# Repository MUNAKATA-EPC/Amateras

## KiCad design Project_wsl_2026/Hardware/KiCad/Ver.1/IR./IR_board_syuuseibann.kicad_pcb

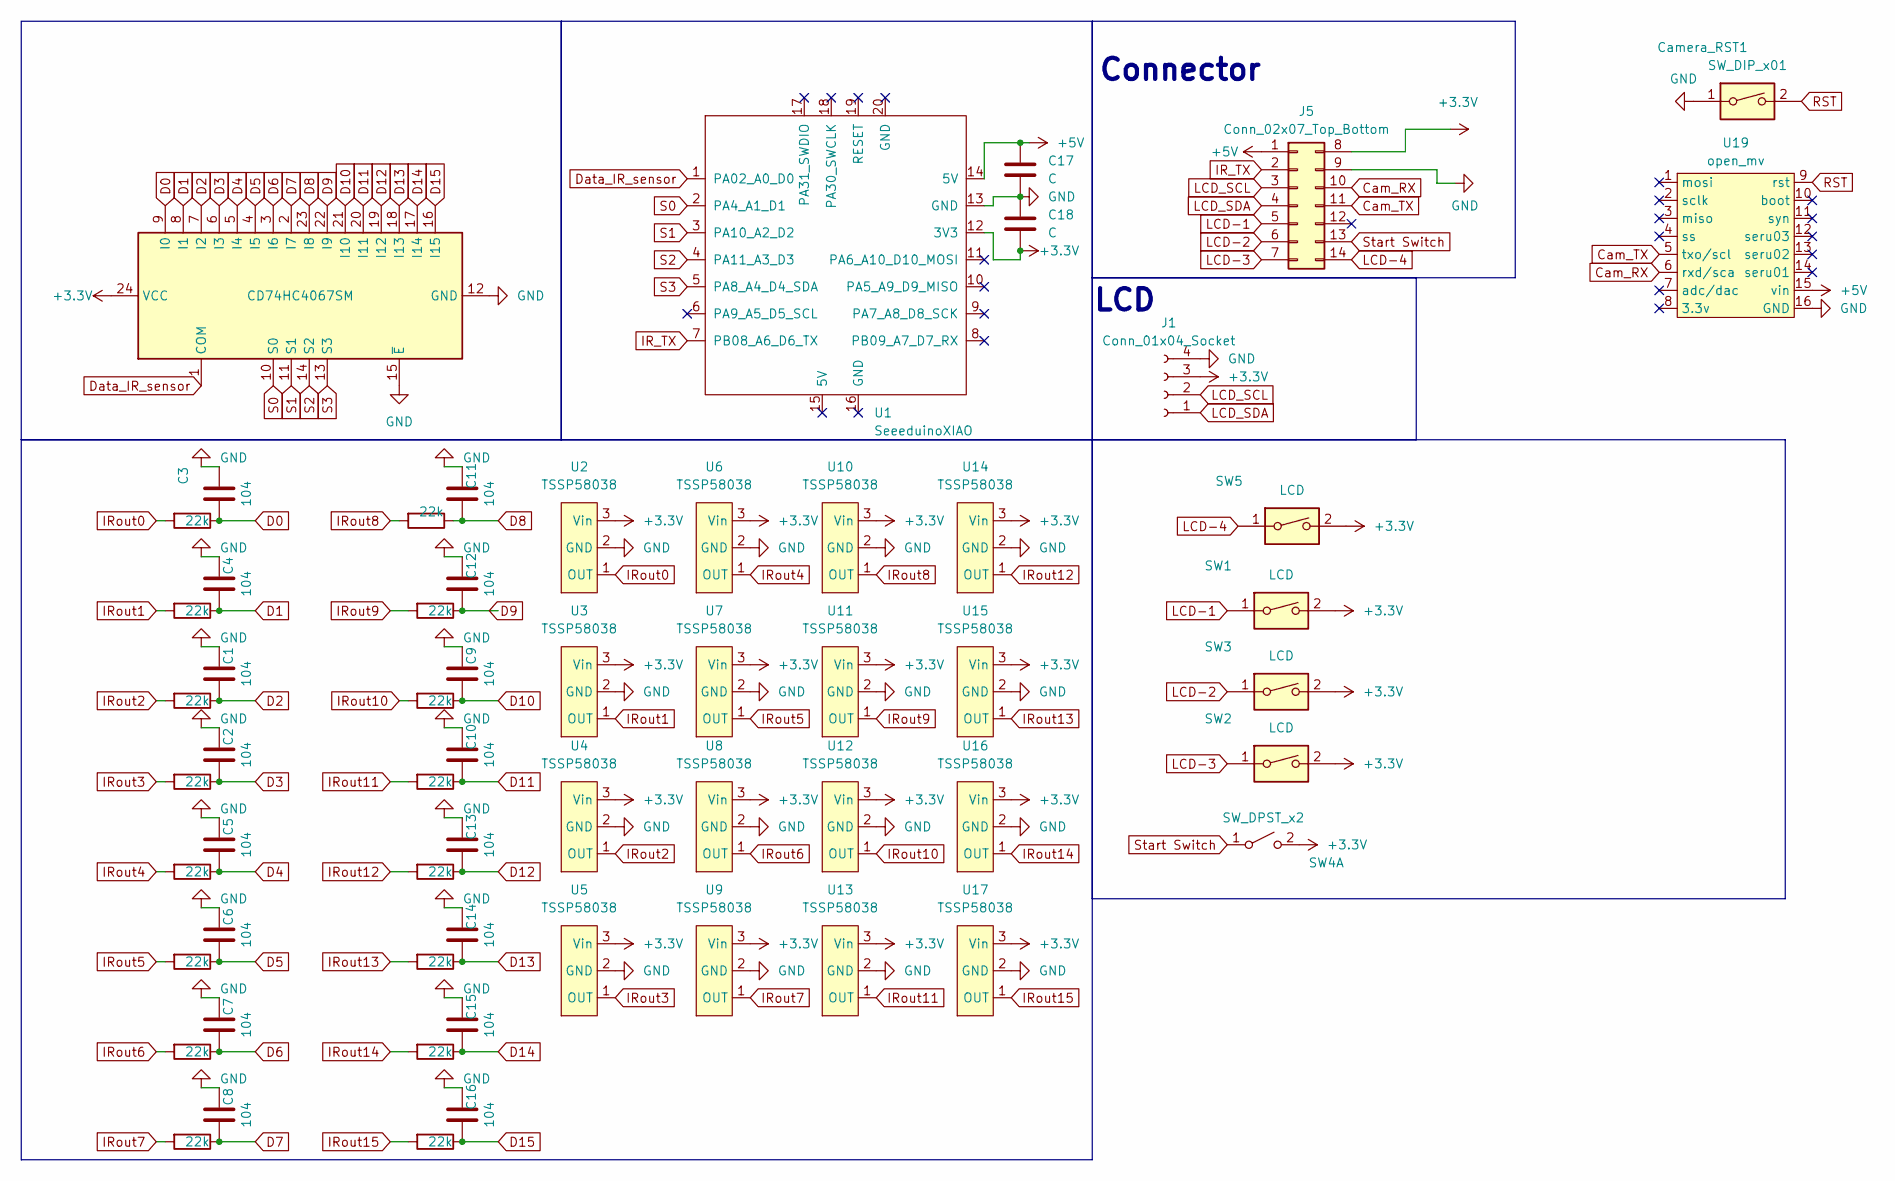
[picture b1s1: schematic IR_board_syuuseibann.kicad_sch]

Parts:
C1, C2, C3, C4, C5, C6, C7, C8, C9, C10, C11, C12, C13, C14, C15, C16: 104; C_0402_1005Metric; LCSC C1525
C17, C18: C; C_Disc_D5.0mm_W2.5mm_P2.50mm
Camera_RST1: SW_DIP_x01; SW_PUSH_6mm_H5mm
J1: Conn_01x04_Socket; PinHeader_1x04_P2.54mm_Vertical
J5: Conn_02x07_Top_Bottom; IDC-Header_2x07_P2.54mm_Vertical
R1, R2, R3, R4, R5, R6, R7, R8, R9, R10, R11, R12, R13, R14, R15, R16: 22k; R_0805_2012Metric; LCSC C25611
SW1, SW2, SW3, SW5: LCD; SW_PUSH_6mm_H5mm
SW4: SW_DPST_x2; PinSocket_1x03_P2.54mm_Vertical
U1: SeeeduinoXIAO; Seeeduino Xiao
U2, U3, U4, U5, U6, U7, U8, U9, U10, U11, U12, U13, U14, U15, U16, U17: TSSP58038; PinHeader_1x03_P2.54mm_Vertical
U18: CD74HC4067SM; SSOP-24_5.3x8.2mm_P0.65mm
U19: open_mv; Open MV

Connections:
+3.3V: C18.2, J1.3, J5.8, SW1.2, SW2.2, SW3.2, SW4.2 (B), SW5.2, U1.12 (3V3), U2.3 (Vin), U3.3 (Vin), U4.3 (Vin), U5.3 (Vin), U6.3 (Vin), U7.3 (Vin), U8.3 (Vin), U9.3 (Vin), U10.3 (Vin), U11.3 (Vin), U12.3 (Vin), U13.3 (Vin), U14.3 (Vin), U15.3 (Vin), U16.3 (Vin), U17.3 (Vin), U18.24 (VCC)
+5V: C17.1, J5.1, U1.14 (5V), U19.15 (vin)
Cam_RX: J5.10, U19.6 (rxd/sca)
Cam_TX: J5.11, U19.5 (txo/scl)
D0: C3.1, R3.1, U18.9 (I0)
D1: C4.1, R4.1, U18.8 (I1)
D2: C1.1, R1.1, U18.7 (I2)
D3: C2.1, R2.1, U18.6 (I3)
D4: C5.1, R5.1, U18.5 (I4)
D5: C6.1, R6.1, U18.4 (I5)
D6: C7.1, R7.1, U18.3 (I6)
D7: C8.1, R8.1, U18.2 (I7)
D8: C11.1, R11.1, U18.23 (I8)
D9: C12.1, R12.1, U18.22 (I9)
D10: C9.1, R9.1, U18.21 (I10)
D11: C10.1, R10.1, U18.20 (I11)
D12: C13.1, R13.1, U18.19 (I12)
D13: C14.1, R14.1, U18.18 (I13)
D14: C15.1, R15.1, U18.17 (I14)
D15: C16.1, R16.1, U18.16 (I15)
Data_IR_sensor: U1.1 (PA02_A0_D0), U18.1 (COM)
GND: C1.2, C2.2, C3.2, C4.2, C5.2, C6.2, C7.2, C8.2, C9.2, C10.2, C11.2, C12.2, C13.2, C14.2, C15.2, C16.2, C17.2, C18.1, Camera_RST1.1, J1.4, J5.9, U1.13 (GND), U2.2 (GND), U3.2 (GND), U4.2 (GND), U5.2 (GND), U6.2 (GND), U7.2 (GND), U8.2 (GND), U9.2 (GND), U10.2 (GND), U11.2 (GND), U12.2 (GND), U13.2 (GND), U14.2 (GND), U15.2 (GND), U16.2 (GND), U17.2 (GND), U18.12 (GND), U18.15 (~E), U19.16 (GND); also elsewhere on the board
IR_TX: J5.2, U1.7 (PB08_A6_D6_TX)
IRout0: R3.2, U2.1 (OUT)
IRout1: R4.2, U3.1 (OUT)
IRout2: R1.2, U4.1 (OUT)
IRout3: R2.2, U5.1 (OUT)
IRout4: R5.2, U6.1 (OUT)
IRout5: R6.2, U7.1 (OUT)
IRout6: R7.2, U8.1 (OUT)
IRout7: R8.2, U9.1 (OUT)
IRout8: R11.2, U10.1 (OUT)
IRout9: R12.2, U11.1 (OUT)
IRout10: R9.2, U12.1 (OUT)
IRout11: R10.2, U13.1 (OUT)
IRout12: R13.2, U14.1 (OUT)
IRout13: R14.2, U15.1 (OUT)
IRout14: R15.2, U16.1 (OUT)
IRout15: R16.2, U17.1 (OUT)
LCD-1: J5.5, SW1.1
LCD-2: J5.6, SW3.1
LCD-3: J5.7, SW2.1
LCD-4: J5.14, SW5.1
LCD_SCL: J1.2, J5.3
LCD_SDA: J1.1, J5.4
RST: Camera_RST1.2, U19.9 (rst); also elsewhere on the board
S0: U1.2 (PA4_A1_D1), U18.10 (S0)
S1: U1.3 (PA10_A2_D2), U18.11 (S1)
S2: U1.4 (PA11_A3_D3), U18.14 (S2)
S3: U1.5 (PA8_A4_D4_SDA), U18.13 (S3)
Start Switch: J5.13, SW4.1 (A)

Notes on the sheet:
LCD
Connector

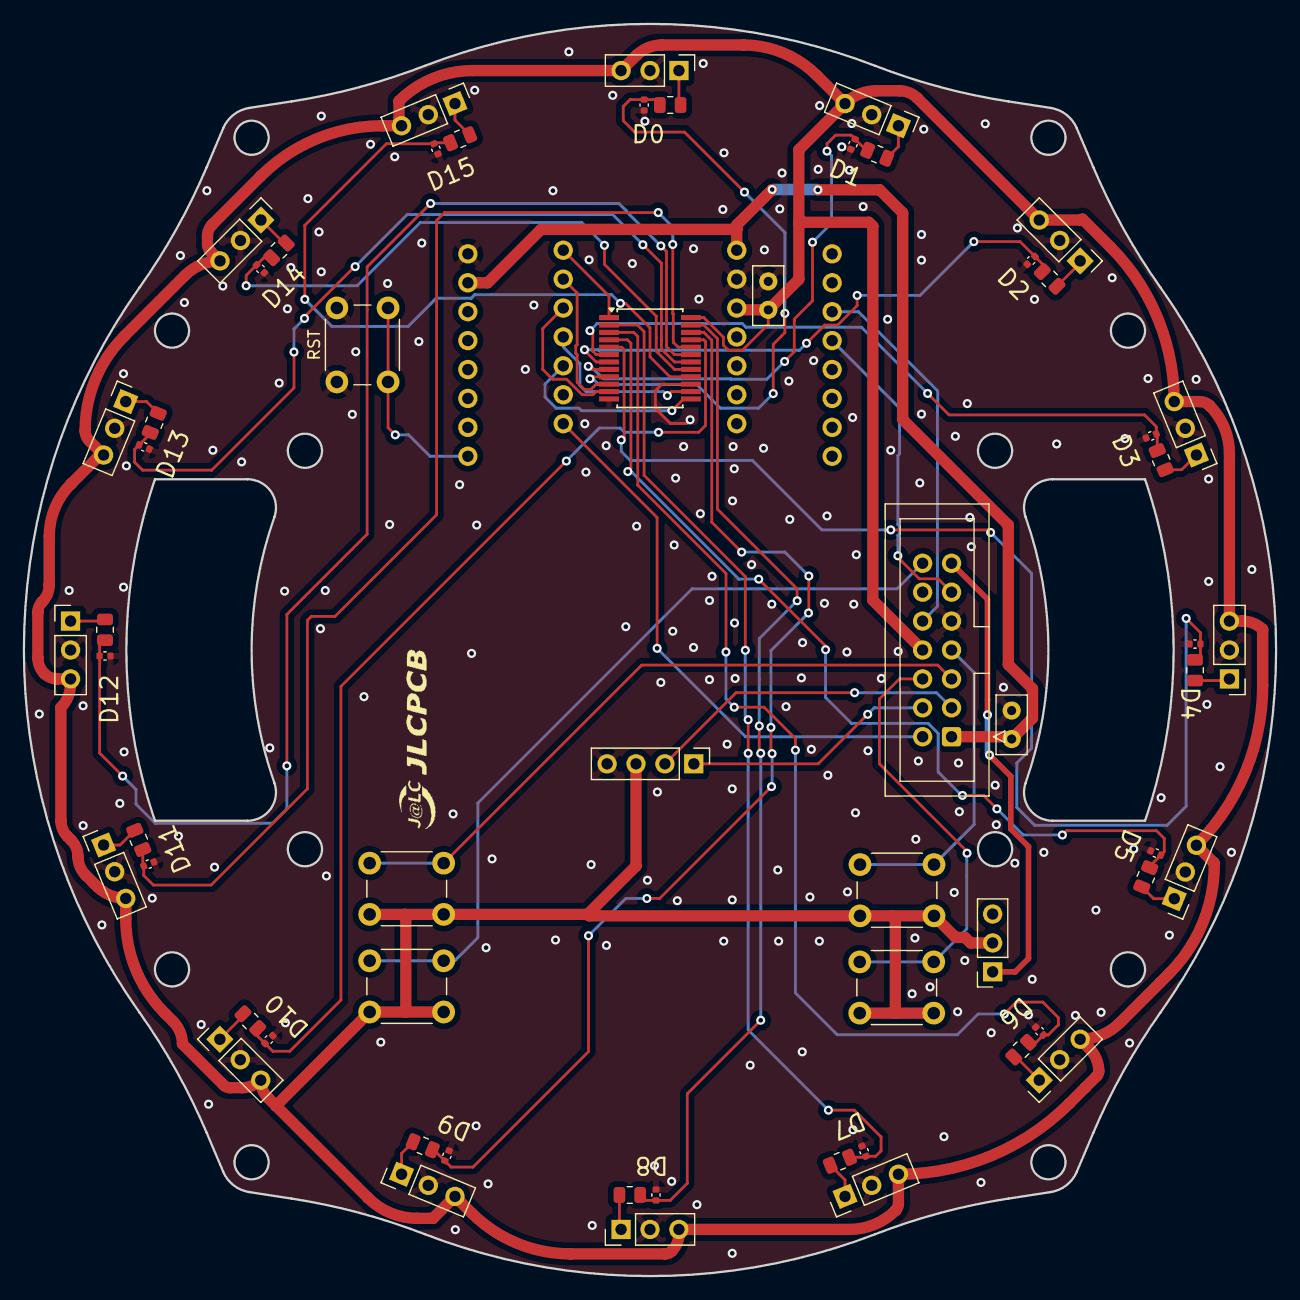
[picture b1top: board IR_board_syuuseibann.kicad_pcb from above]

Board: 2 copper layers, 110.0 x 110.0 mm, 61 parts (1 on the bottom side), 51 nets.

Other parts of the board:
RST: SW_DIP_x01; SW_PUSH_6mm_H5mm

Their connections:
GND: RST.1; also elsewhere on the board
RST: RST.2; also elsewhere on the board

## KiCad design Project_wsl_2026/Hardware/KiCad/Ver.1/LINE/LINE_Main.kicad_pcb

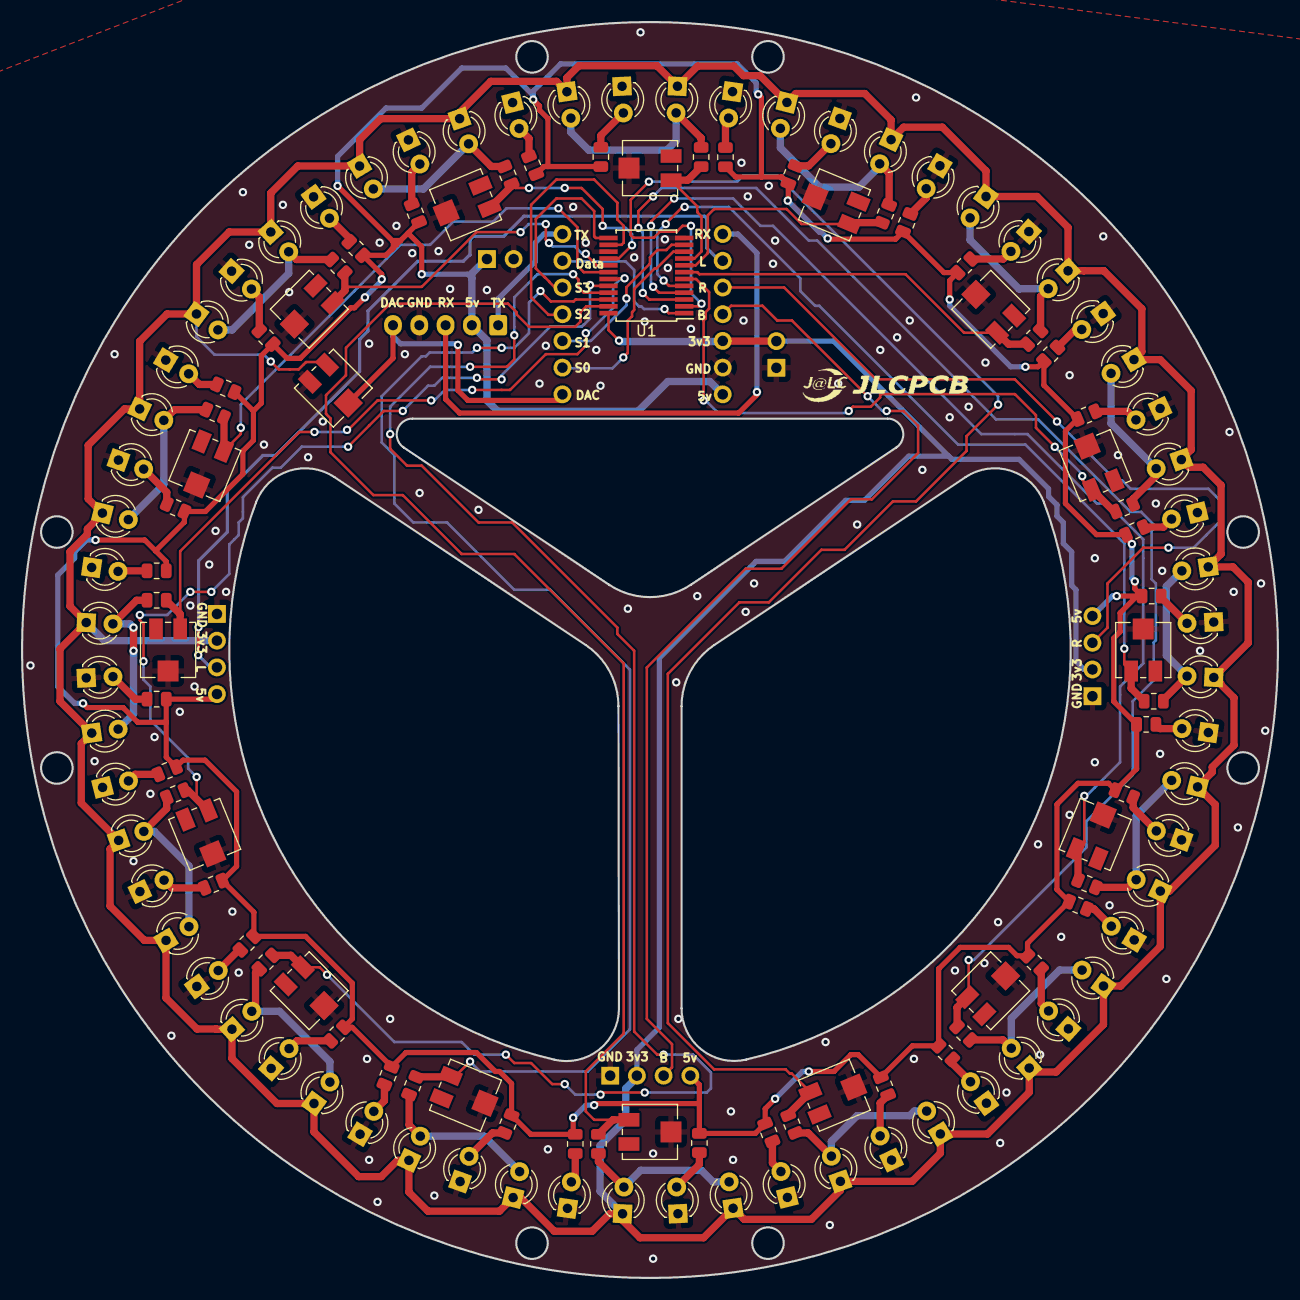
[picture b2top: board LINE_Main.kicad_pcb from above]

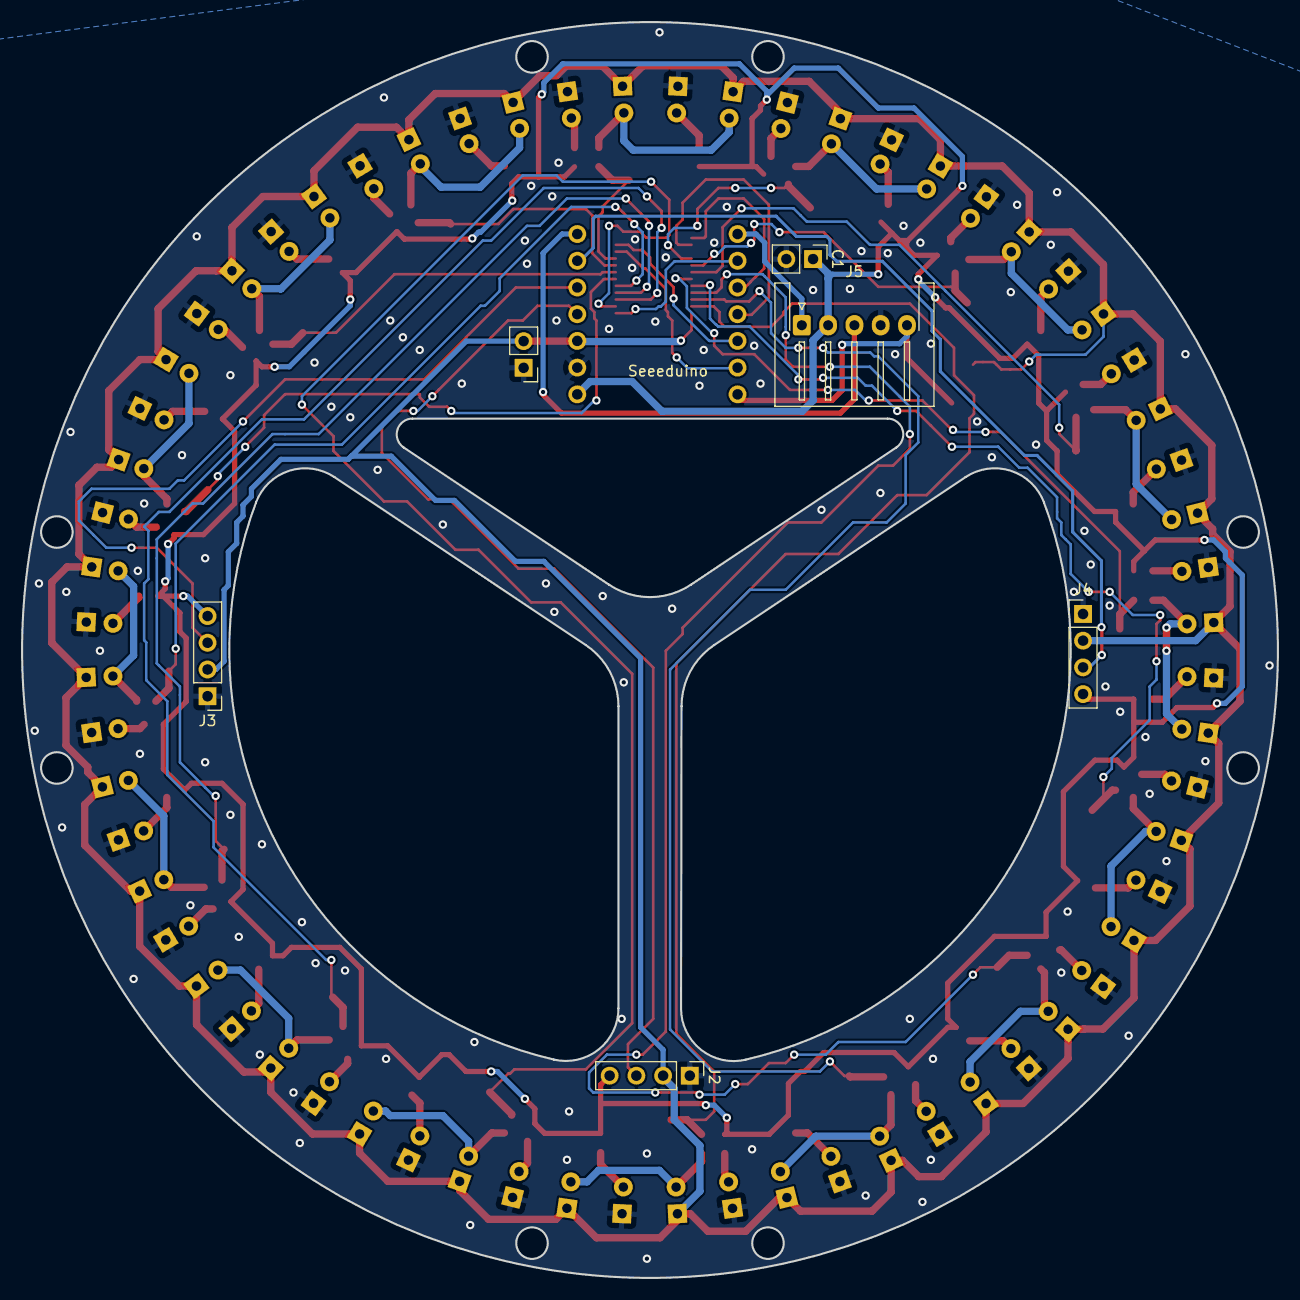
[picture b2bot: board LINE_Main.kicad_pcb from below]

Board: 2 copper layers, 119.4 x 119.4 mm, 137 parts (6 on the bottom side), 78 nets.

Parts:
C1, C2: C; PinHeader_1x02_P2.54mm_Vertical
D1, D2, D3, D4, D5, D6, D7, D8, D9, D10, D11, D12, D13, D14, D15, D16, D17, D18, D19, D20, D21, D22, D23, D24, D25, D26, D27, D28, D29, D30, D31, D32: LED; LED_D3.0mm_Clear
J2, J3, J4: Conn_01x04_Socket; PinHeader_1x04_P2.54mm_Vertical
J5: Conn_01x05_Socket; JST_XH_S5B-XH-A-1_1x05_P2.50mm_Horizontal
Q1, Q2, Q3, Q4, Q5, Q6, Q7, Q8, Q9, Q10, Q11, Q12, Q13, Q14, Q15, Q16, Q17, Q18, Q19, Q20, Q21, Q22, Q23, Q24, Q25, Q26, Q27, Q28, Q29, Q30, Q31, Q32: Q_Photo_NPN; LED_D3.0mm_Clear
R1, R2, R3, R4, R5, R6, R7, R8, R9, R10, R11, R12, R13, R14, R15, R16, R17, R18, R19, R20, R21, R22, R23, R24, R25, R26, R27, R28, R29, R30, R31, R32, R33, R34, R35, R36, R37, R38, R39, R40, R41, R42, R43, R44, R45, R46, R47, R48: R; R_0805_2012Metric
RV1, RV2, RV3, RV4, RV5, RV6, RV7, RV8, RV9, RV10, RV11, RV12, RV13, RV14, RV15, RV16, RV17: R_Potentiometer_Trim_US; Potentiometer_Vishay_TS53YJ_Vertical
U1: CD74HC4067SM; SSOP-24_5.3x8.2mm_P0.65mm
U2: Seeeduino_Xiao; Seeeduino Xiao v2

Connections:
1: R1.2, RV1.3, U1.9 (I0)
2: R2.2, RV2.3, U1.8 (I1)
3: R3.2, RV3.3, U1.7 (I2)
4: R4.2, RV4.3, U1.6 (I3)
5: R5.2, RV5.3, U1.5 (I4)
6: R6.2, RV6.3, U1.4 (I5)
7: R7.2, RV7.3, U1.3 (I6)
8: R8.2, RV8.3, U1.2 (I7)
9: R9.2, RV9.3, U1.23 (I8)
10: R10.2, RV10.3, U1.22 (I9)
11: R11.2, RV11.3, U1.21 (I10)
12: R12.2, RV12.3, U1.20 (I11)
13: R13.2, RV13.3, U1.19 (I12)
14: R14.2, RV14.3, U1.18 (I13)
15: R15.2, RV15.3, U1.17 (I14)
16: R16.2, RV16.3, U1.16 (I15)
+3.3V: C2.2, J2.2, J3.2, J4.2, Q1.1 (C), Q2.1 (C), Q3.1 (C), Q4.1 (C), Q5.1 (C), Q6.1 (C), Q7.1 (C), Q8.1 (C), Q9.1 (C), Q10.1 (C), Q11.1 (C), Q12.1 (C), Q13.1 (C), Q14.1 (C), Q15.1 (C), Q16.1 (C), Q17.1 (C), Q18.1 (C), Q19.1 (C), Q20.1 (C), Q21.1 (C), Q22.1 (C), Q23.1 (C), Q24.1 (C), Q25.1 (C), Q26.1 (C), Q27.1 (C), Q28.1 (C), Q29.1 (C), Q30.1 (C), Q31.1 (C), Q32.1 (C), RV17.3, U1.24 (VCC), U2.12 (3V3)
+5V: C1.1, J2.4, J3.4, J4.4, J5.2, R17.1, R18.1, R19.1, R20.1, R21.1, R22.1, R23.1, R24.1, R25.1, R26.1, R27.1, R28.1, R29.1, R30.1, R31.1, R32.1, R33.1, R34.1, R35.1, R36.1, R37.1, R38.1, R39.1, R40.1, R41.1, R42.1, R43.1, R44.1, R45.1, R46.1, R47.1, R48.1, U2.14 (5V)
DAC: J5.5, RV17.2, U2.1 (DAC)
Data_Line_sensor: U1.1 (COM), U2.6 (SCL)
GND: C1.2, C2.1, D1.1 (K), D2.1 (K), D3.1 (K), D4.1 (K), D5.1 (K), D6.1 (K), D7.1 (K), D8.1 (K), D9.1 (K), D10.1 (K), D11.1 (K), D12.1 (K), D13.1 (K), D14.1 (K), D15.1 (K), D16.1 (K), D17.1 (K), D18.1 (K), D19.1 (K), D20.1 (K), D21.1 (K), D22.1 (K), D23.1 (K), D24.1 (K), D25.1 (K), D26.1 (K), D27.1 (K), D28.1 (K), D29.1 (K), D30.1 (K), D31.1 (K), D32.1 (K), J2.1, J3.1, J4.1, J5.4, RV1.2, RV2.2, RV3.2, RV4.2, RV5.2, RV6.2, RV7.2, RV8.2, RV9.2, RV10.2, RV11.2, RV12.2, RV13.2, RV14.2, RV15.2, RV16.2, RV17.1, U1.12 (GND), U1.15 (~E), U2.13 (GND)
Line_RX: J5.3, U2.8 (RX)
Line_TX: J5.1, U2.7 (TX)
unnamed: D1.2 (A), R17.2
unnamed: D2.2 (A), R18.2
unnamed: D3.2 (A), R19.2
unnamed: D4.2 (A), R20.2
unnamed: D5.2 (A), R21.2
unnamed: D6.2 (A), R22.2
unnamed: D7.2 (A), R23.2
unnamed: D8.2 (A), R24.2
unnamed: D9.2 (A), R25.2
unnamed: D10.2 (A), R26.2
unnamed: D11.2 (A), R27.2
unnamed: D12.2 (A), R28.2
unnamed: D13.2 (A), R29.2
unnamed: D14.2 (A), R30.2
unnamed: D15.2 (A), R31.2
unnamed: D16.2 (A), R32.2
unnamed: D17.2 (A), R33.2
unnamed: D18.2 (A), R34.2
unnamed: D19.2 (A), R35.2
unnamed: D20.2 (A), R36.2
unnamed: D21.2 (A), R37.2
unnamed: D22.2 (A), R38.2
unnamed: D23.2 (A), R39.2
unnamed: D24.2 (A), R40.2
unnamed: D25.2 (A), R41.2
unnamed: D26.2 (A), R42.2
unnamed: D27.2 (A), R43.2
unnamed: D28.2 (A), R44.2
unnamed: D29.2 (A), R45.2
unnamed: D30.2 (A), R46.2
unnamed: D31.2 (A), R47.2
unnamed: D32.2 (A), R48.2
unnamed: Q1.2 (E), Q2.2 (E), R1.1
unnamed: Q3.2 (E), Q4.2 (E), R2.1
unnamed: Q5.2 (E), Q6.2 (E), R3.1
unnamed: Q7.2 (E), Q8.2 (E), R4.1
unnamed: Q9.2 (E), Q10.2 (E), R5.1
unnamed: Q11.2 (E), Q12.2 (E), R6.1
unnamed: Q13.2 (E), Q14.2 (E), R7.1
unnamed: Q15.2 (E), Q16.2 (E), R8.1
unnamed: Q17.2 (E), Q18.2 (E), R9.1
unnamed: Q19.2 (E), Q20.2 (E), R10.1
unnamed: Q21.2 (E), Q22.2 (E), R11.1
unnamed: Q23.2 (E), Q24.2 (E), R12.1
unnamed: Q25.2 (E), Q26.2 (E), R13.1
unnamed: Q27.2 (E), Q28.2 (E), R14.1
unnamed: Q29.2 (E), Q30.2 (E), R15.1
unnamed: Q31.2 (E), Q32.2 (E), R16.1
S0: U1.10 (S0), U2.2
S1: U1.11 (S1), U2.3
S2: U1.14 (S2), U2.4
S3: U1.13 (S3), U2.5 (SDA)
Sensor_Back: J2.3, U2.11 (MOSI)
Sensor_Left: J4.3, U2.9 (SCK)
Sensor_Right: J3.3, U2.10 (MISO)

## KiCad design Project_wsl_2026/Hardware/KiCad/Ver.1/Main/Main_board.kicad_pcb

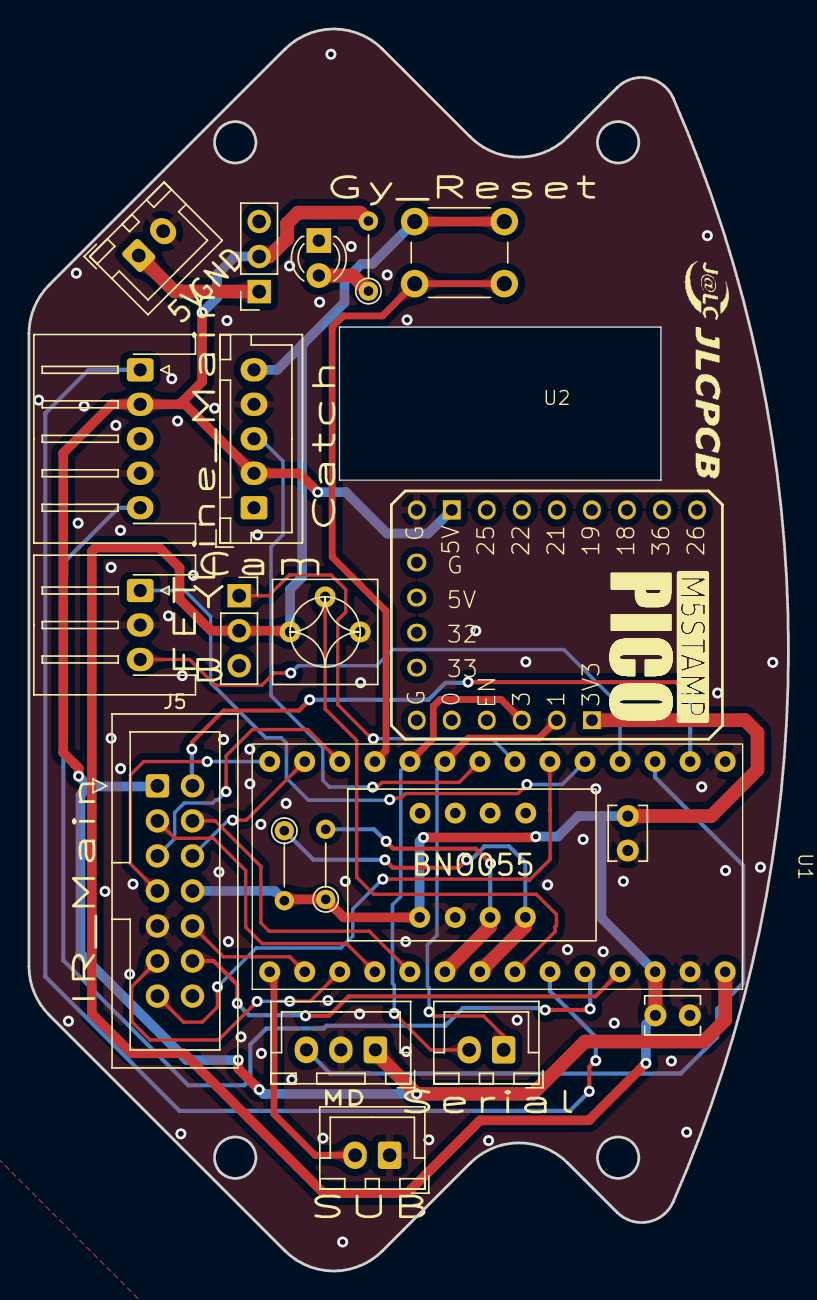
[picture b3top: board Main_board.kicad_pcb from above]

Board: 2 copper layers, 55.1 x 90.0 mm, 21 parts (0 on the bottom side), 29 nets.

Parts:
BNO1: BNO055
C1, C3: C; C_Disc_D3.8mm_W2.6mm_P2.50mm
D1: LED; LED_D3.0mm_Clear
J1: Conn_01x03_Socket; JST_XH_B3B-XH-A_1x03_P2.50mm_Vertical
J2, J6, J7: Conn_01x02_Socket; JST_XH_B2B-XH-A_1x02_P2.50mm_Vertical
J3: Conn_01x03_Socket; JST_XH_S3B-XH-A-1_1x03_P2.50mm_Horizontal
J4: Conn_01x05_Socket; JST_XH_S5B-XH-A-1_1x05_P2.50mm_Horizontal
J5: Conn_02x07_Top_Bottom; IDC-Header_2x07_P2.54mm_Vertical
J8: Conn_01x05_Socket; JST_XH_B5B-XH-A_1x05_P2.50mm_Vertical
R1, R2: 10K; R_Axial_DIN0204_L3.6mm_D1.6mm_P5.08mm_Vertical
R3: R; R_Axial_DIN0204_L3.6mm_D1.6mm_P5.08mm_Vertical
RV1: R_Potentiometer_Trim_US; RV
SW1: SW_Push; SW_PUSH_6mm_H5mm
SW2, SW4: SW_DPST_x2; PinSocket_1x03_P2.54mm_Vertical
U1: Teensy4.0
U2: Stamp_Pico; Stamp Pico

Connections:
5V_IN: J2.1, SW4.1 (A)
+3.3V: BNO1.1 (VIN), C1.1, C3.2, J5.8, J8.5, R1.1, R2.2, RV1.3, SW1.1, SW2.2 (B), U1.31 (3V3), U2.19 (3V3)
+5V: J1.1, J4.2, J5.1, J8.2, R3.2, SW4.2 (B), U1.33 (VIN), U2.8 (5V)
A6: RV1.2, U1.27 (20_A6_TX5_LRCLK1)
Cam Switch: SW2.1 (A), U1.7 (5_IN2)
Cam_RX: J5.10, U1.21 (14_A0_TX3_SPDIF_OUT)
Cam_TX: J5.11, U1.22 (15_A1_RX3_SPDIF_IN)
Catch: J8.3, U1.8 (6_OUT1D)
Catch_sub: J7.2, U1.20 (13_SCK_CRX1_LED)
FET_1: J3.3, U1.4 (2_OUT2)
FET_2: J3.1, U1.5 (3_LRCLK2)
GND: BNO1.2 (GND), C1.2, C3.1, D1.1 (K), J1.2, J2.2, J3.2, J4.4, J5.9, J7.1, J8.4, RV1.1, U1.1 (GND), U2.9 (GND)
Gyro_SCL: BNO1.4 (SCL), R2.1, U1.26 (19_A5_SCL0)
Gyro_SDA: BNO1.3 (SDA), R1.2, U1.25 (18_A4_SDA0)
Gyro_reset: SW1.2, U1.11 (9_OUT1C)
IR_DAC: J5.12, U1.30 (23_A9_CRX1_MCLK1)
IR_TX: J5.2, U1.2 (0_RX1_CRX2_CS1)
LCD-1: J5.5, U1.12 (10_CS_MQSR)
LCD-2: J5.6, U1.13 (11_MOSI_CTX1)
LCD-3: J5.7, U1.14 (12_MISO_MQSL)
LCD_SCL: J5.3, U1.23 (16_A2_RX4_SCL1)
LCD_SDA: J5.4, U1.24 (17_A3_TX4_SDA1)
Line_DAC: J4.5, U1.29 (22_A8_CTX1)
Line_TX: J4.1, U1.28 (21_A7_RX5_BCLK1)
unnamed: D1.2 (A), R3.1
RX2: J6.1, U1.9 (7_RX2_OUT1A), U2.18 (G1)
Start Switch: J5.13, U1.6 (4_BCLK2)
TX2: J6.2, U1.10 (8_TX2_IN1), U2.17 (G3)
TX_MD: J1.3, U1.3 (1_TX1_CTX2_MISO1)

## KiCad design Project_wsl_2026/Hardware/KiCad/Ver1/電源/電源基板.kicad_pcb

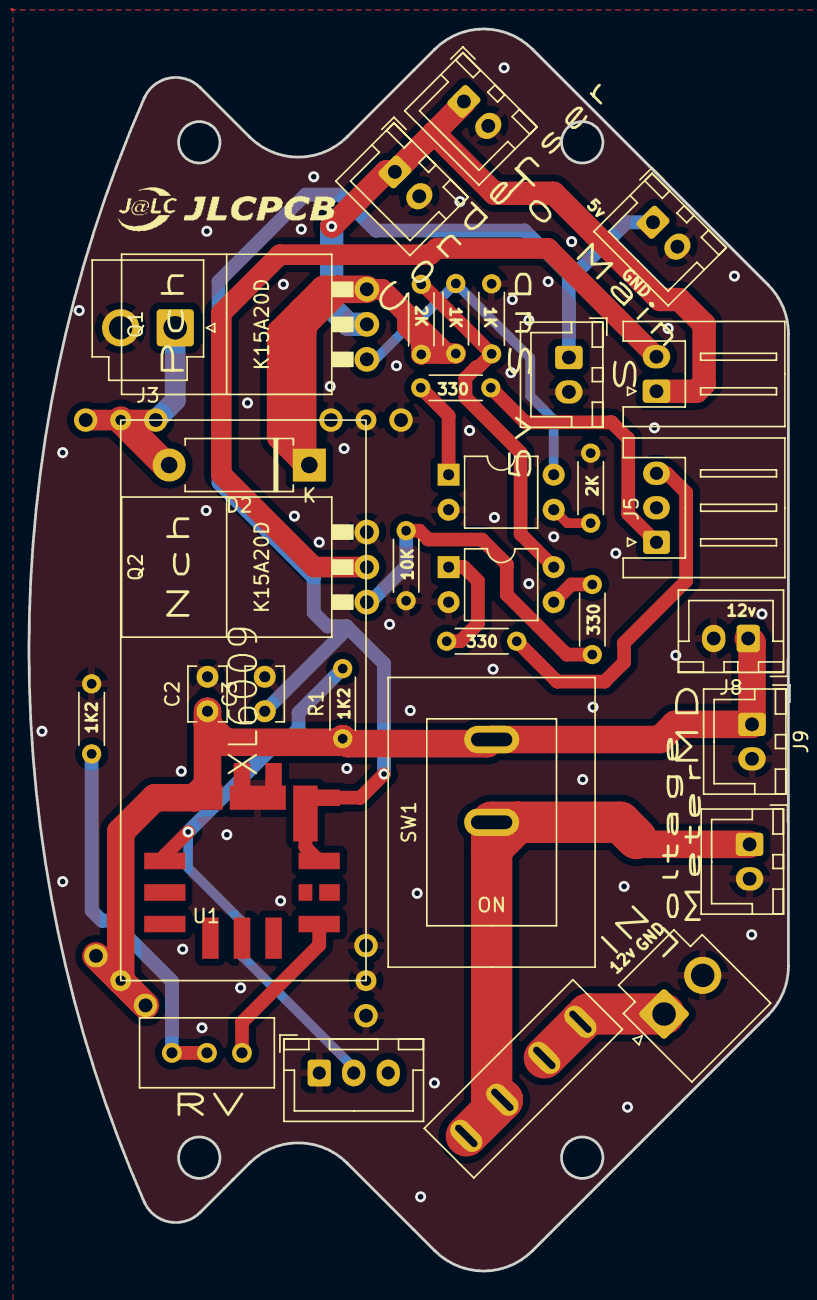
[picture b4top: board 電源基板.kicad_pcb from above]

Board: 2 copper layers, 55.1 x 90.0 mm, 34 parts (0 on the bottom side), 21 nets.

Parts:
BT1: Battery; JST_VH_B2P-VH_1x02_P3.96mm_Vertical
C1, C4: C; JST_XH_B2B-XH-A_1x02_P2.50mm_Vertical
C2, C3: C; C_Disc_D3.8mm_W2.6mm_P2.50mm
D2: D; D_DO-15_P10.16mm_Horizontal
F1: Fuse; fuse_socket
J1, J4, J8, J9: Conn_01x02_Socket; JST_XH_B2B-XH-A_1x02_P2.50mm_Vertical
J3: Conn_01x02_Socket; JST_VH_B2P-VH_1x02_P3.96mm_Vertical
J5: Conn_01x03_Socket; JST_XH_S3B-XH-A_1x03_P2.50mm_Horizontal
J6: 電圧計; JST_XH_B2B-XH-A_1x02_P2.50mm_Vertical
J7: Conn_01x02_Socket; JST_XH_S2B-XH-A_1x02_P2.50mm_Horizontal
Q1: PMOS; K15A20D
Q2: NMOS; K15A20D
R1, R2: R; R_Axial_DIN0204_L3.6mm_D1.6mm_P5.08mm_Horizontal
R3, R7: 2K; R_Axial_DIN0204_L3.6mm_D1.6mm_P5.08mm_Horizontal
R4, R8: 1K; R_Axial_DIN0204_L3.6mm_D1.6mm_P5.08mm_Horizontal
R5, R6, R9: 330; R_Axial_DIN0204_L3.6mm_D1.6mm_P5.08mm_Horizontal
R10: 10K; R_Axial_DIN0204_L3.6mm_D1.6mm_P5.08mm_Horizontal
RV1: R_Potentiometer_Trim_US; Potentiometer_Bourns_3296W_Vertical
SW1: SW_DIP_x01; DS-850k
SW2: SW_DIP_x01; JST_XH_B3B-XH-A_1x03_P2.50mm_Vertical
U1: OKL-T_6-W12N-C; DCDC-murata-6A
U2: XL6009
U3, U4: EL817; DIP-4_W7.62mm

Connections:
48kana: D2.2 (A), J3.1, U2.3 (OUT＋)
+5V: C3.1, J1.1, J4.1, U1.4 (VOUT), U1.5 (SENSE)
+12V: C2.1, J8.1, J9.1, R1.1, SW1.2, U1.2 (VIN), U2.1 (IN＋)
+15V: R3.2, R4.1, U4.4
+48V: D2.1 (K), Q1.3 (S), R3.1, R8.1
FET1: J5.1, R5.1
FET２: J5.3, R6.1
GND: BT1.2 (-), C1.2, C2.2, C3.2, C4.2, J1.2, J3.2, J4.2, J5.2, J6.2, J8.2, J9.2, Q2.3 (S), R2.2, R4.2, R7.2, R10.2, SW2.1, U1.3 (GND), U1.7 (GND), U2.2 (IN－), U2.4 (OUT－), U3.2, U4.2
unnamed: BT1.1 (+), F1.1
unnamed: F1.2, J6.1, SW1.1
unnamed: Q1.2 (G), R8.2, U3.4
unnamed: Q2.2 (G), R9.1, R10.1
unnamed: R2.1, RV1.1, RV1.2
unnamed: R5.2, U3.1
unnamed: R6.2, U4.1
unnamed: R7.1, U3.3
unnamed: R9.2, U4.3
unnamed: R1.2, SW2.2, U1.1 (ON/OFF_CTRL)
unnamed: RV1.3, U1.6 (TRIM)
Solenoid+: C1.1, C4.1, J7.1, Q1.1 (D)
Solenoid-: J7.2, Q2.1 (D)

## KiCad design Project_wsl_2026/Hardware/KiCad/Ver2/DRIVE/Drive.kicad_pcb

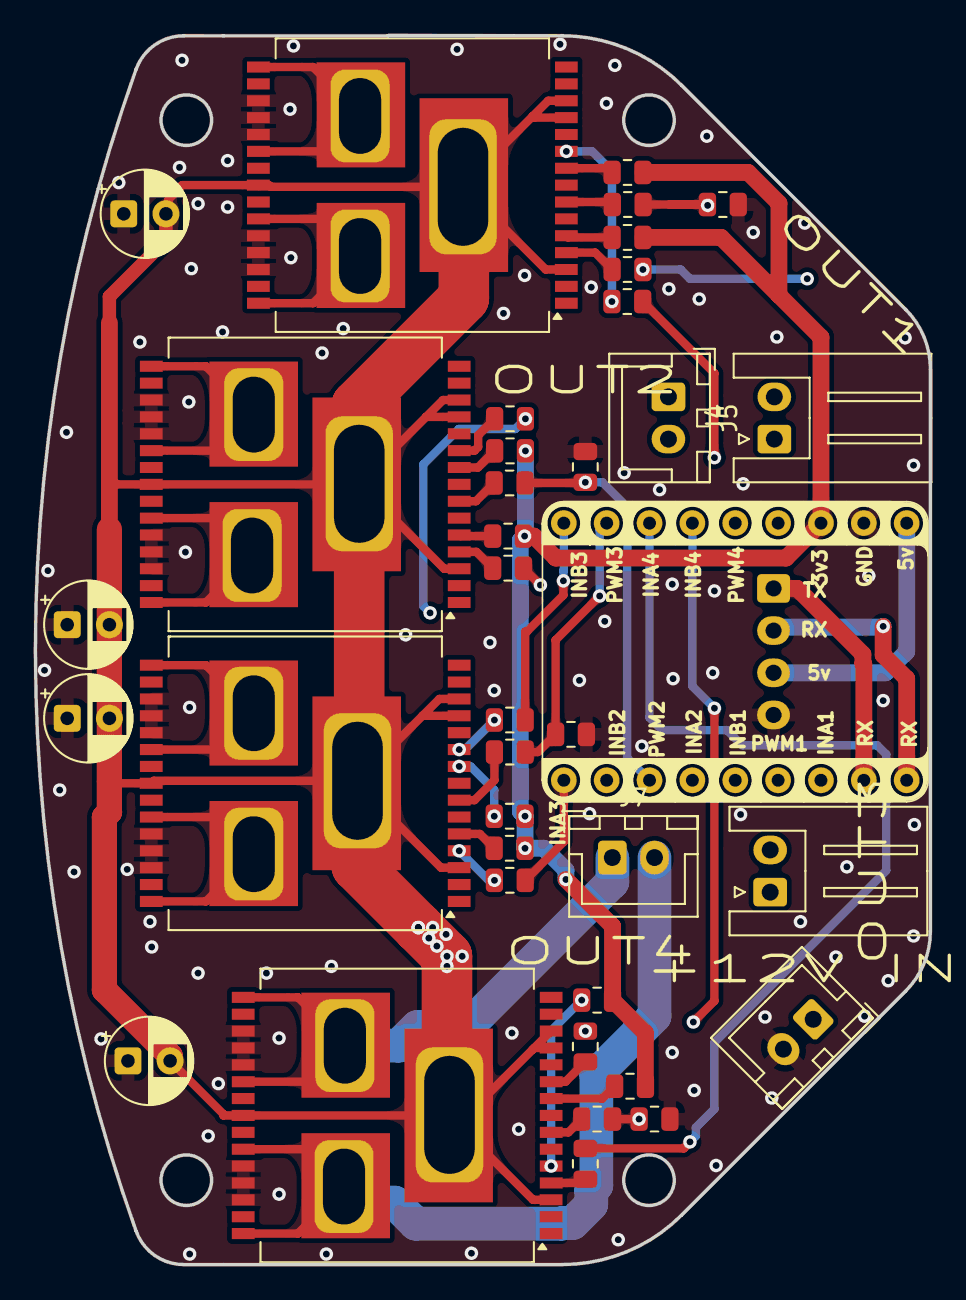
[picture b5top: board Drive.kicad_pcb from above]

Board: 4 copper layers, 53.0 x 72.8 mm, 39 parts (1 on the bottom side), 46 nets.

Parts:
C1, C2, C4, C5: C; CP_Radial_D5.0mm_P2.50mm
J2: Conn_01x04_Socket; JST_XH_S4B-XH-A_1x04_P2.50mm_Horizontal
J3, J5, J7: Conn_01x02_Socket; JST_XH_B2B-XH-A_1x02_P2.50mm_Vertical
J4, J6: Conn_01x02_Socket; JST_XH_S2B-XH-A_1x02_P2.50mm_Horizontal
R1, R7, R13, R21: 10k; R_0805_2012Metric
R2, R6, R8, R12, R14, R18, R22, R28: 4.7k; R_0805_2012Metric
R3, R4, R5, R9, R10, R11, R15, R16, R17, R23, R24, R25: 1k; R_0805_2012Metric
U1: RP2040ZERO
U2, U3, U5, U8: VNH5019A-E; ST_MultiPowerSO-30

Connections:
+3.3V: R2.2, R6.2, R8.2, R12.2, R14.2, R18.2, R22.2, R28.2, U1.3 (3.3v)
+5V: J2.3, U1.1 (5v)
+12V: C1.2, C2.2, C4.2, C5.2, J3.1, U2.3 (VCC), U2.12 (VBAT), U2.13 (VCC), U2.23 (VCC), U2.31 (VCC), U3.3 (VCC), U3.12 (VBAT), U3.13 (VCC), U3.23 (VCC), U3.31 (VCC), U5.3 (VCC), U5.12 (VBAT), U5.13 (VCC), U5.23 (VCC), U5.31 (VCC), U8.3 (VCC), U8.12 (VBAT), U8.13 (VCC), U8.23 (VCC), U8.31 (VCC)
/INA_1: R3.2, U1.21 (GP2/SDA)
/INA_2: R9.2, U1.18 (GP5/RX1/SCl)
/INA_3: R15.2, U1.15 (GP8/TX1/SDA)
/INA_4: R23.2, U1.7 (GP26/ADC0/SDA)
/INB_1: R4.2, U1.19 (GP4/TX1/SDA)
/INB_2: R10.2, U1.16 (GP7/SCL)
/INB_3: R16.2, U1.9 (GP14/SDA)
/INB_4: R24.2, U1.6 (GP27/ADC1/SCL)
/MD_RX: J2.2, U1.23 (GP0/TX0/SDA)
/MD_TX: J2.1, U1.22 (GP1/RX0/SCL)
/OUTA_1: J4.2, U2.1 (OUTA), U2.25 (OUTA), U2.30 (OUTA), U2.33 (OUTA)
/OUTA_2: J5.2, U3.1 (OUTA), U3.25 (OUTA), U3.30 (OUTA), U3.33 (OUTA)
/OUTA_3: J6.2, U5.1 (OUTA), U5.25 (OUTA), U5.30 (OUTA), U5.33 (OUTA)
/OUTA_4: J7.2, U8.1 (OUTA), U8.25 (OUTA), U8.30 (OUTA), U8.33 (OUTA)
/OUTB_1: J4.1, U2.15 (OUTB), U2.16 (OUTB), U2.21 (OUTB), U2.32 (OUTB)
/OUTB_2: J5.1, U3.15 (OUTB), U3.16 (OUTB), U3.21 (OUTB), U3.32 (OUTB)
/OUTB_3: J6.1, U5.15 (OUTB), U5.16 (OUTB), U5.21 (OUTB), U5.32 (OUTB)
/OUTB_4: J7.1, U8.15 (OUTB), U8.16 (OUTB), U8.21 (OUTB), U8.32 (OUTB)
/PWM_1: R1.1, R5.2, U1.20 (GP3/SCL)
/PWM_2: R7.1, R11.2, U1.17 (GP6/SDA)
/PWM_3: R13.1, R17.2, U1.8 (GP15/SCL)
/PWM_4: R21.1, R25.2, U1.5 (GP28/ADC2)
GND: C1.1, C2.1, C4.1, C5.1, J2.4, J3.2, R1.2, R7.2, R13.2, R21.2, U1.2 (GND), U2.18 (GNDB), U2.19 (GNDB), U2.20 (GNDB), U2.26 (GNDA), U2.27 (GNDA), U2.28 (GNDA), U3.18 (GNDB), U3.19 (GNDB), U3.20 (GNDB), U3.26 (GNDA), U3.27 (GNDA), U3.28 (GNDA), U5.18 (GNDB), U5.19 (GNDB), U5.20 (GNDB), U5.26 (GNDA), U5.27 (GNDA), U5.28 (GNDA), U8.18 (GNDB), U8.19 (GNDB), U8.20 (GNDB), U8.26 (GNDA), U8.27 (GNDA), U8.28 (GNDA)
unnamed: R2.1, U2.5 (EN/DIAGA)
unnamed: R6.1, U2.9 (EN/DIAGB)
unnamed: R3.1, U2.4 (INA)
unnamed: R4.1, U2.10 (INB)
unnamed: R5.1, U2.7 (PWM)
unnamed: R8.1, U3.5 (EN/DIAGA)
unnamed: R12.1, U3.9 (EN/DIAGB)
unnamed: R9.1, U3.4 (INA)
unnamed: R10.1, U3.10 (INB)
unnamed: R11.1, U3.7 (PWM)
unnamed: R14.1, U5.5 (EN/DIAGA)
unnamed: R18.1, U5.9 (EN/DIAGB)
unnamed: R15.1, U5.4 (INA)
unnamed: R16.1, U5.10 (INB)
unnamed: R17.1, U5.7 (PWM)
unnamed: R22.1, U8.5 (EN/DIAGA)
unnamed: R28.1, U8.9 (EN/DIAGB)
unnamed: R23.1, U8.4 (INA)
unnamed: R24.1, U8.10 (INB)
unnamed: R25.1, U8.7 (PWM)
